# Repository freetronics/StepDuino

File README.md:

Freetronics StepDuino
=====================
Copyright 2013 Freetronics Pty Ltd  
Freetronics site:  www.freetronics.com  
Freetronics email: info@freetronics.com  

The StepDuino is an Arduino-compatible board with two onboard stepper
motor drivers, a 20x4 LCD, servo outputs, and an SD card slot. This
makes it ideal for mechatronics projects such as small robots or 2D
plotters.

It uses the same ATmega328P MCU as the Arduino Uno reference design,
and includes an ATmega16u2 USB-to-serial converter just like the Uno.
You can therefore program it the same way as you would an Uno, but
with the benefit of all the extra features built in to the StepDuino.

Features:

 * 2 x 4-wire stepper motor drivers
 * 20x4 LCD
 * Micro SD card slot
 * Analog inputs for use with Nintendo DS touch screen or other sensors

You can view more online at:

  http://www.freetronics.com/stepduino

INSTALLATION
------------
The design is saved as an EAGLE project. EAGLE PCB design software is
available from www.cadsoftusa.com free for non-commercial use. To use
this project download it and place the directory containing these files
into the "eagle" directory on your computer. Then open EAGLE and
navigate to Projects -> eagle -> StepDuino.

DISTRIBUTION
------------
The specific terms of distribution of this project are governed by the
license referenced below.

LICENSE
-------
Licensed under the TAPR Open Hardware License (www.tapr.org/OHL).
The "license" folder within this repository also contains a copy of
this license in plain text format.

CREDITS
-------
Designed by Luke Weston (reindeerflotilla@gmail.com) and Jonathan Oxer
(jon@freetronics.com)

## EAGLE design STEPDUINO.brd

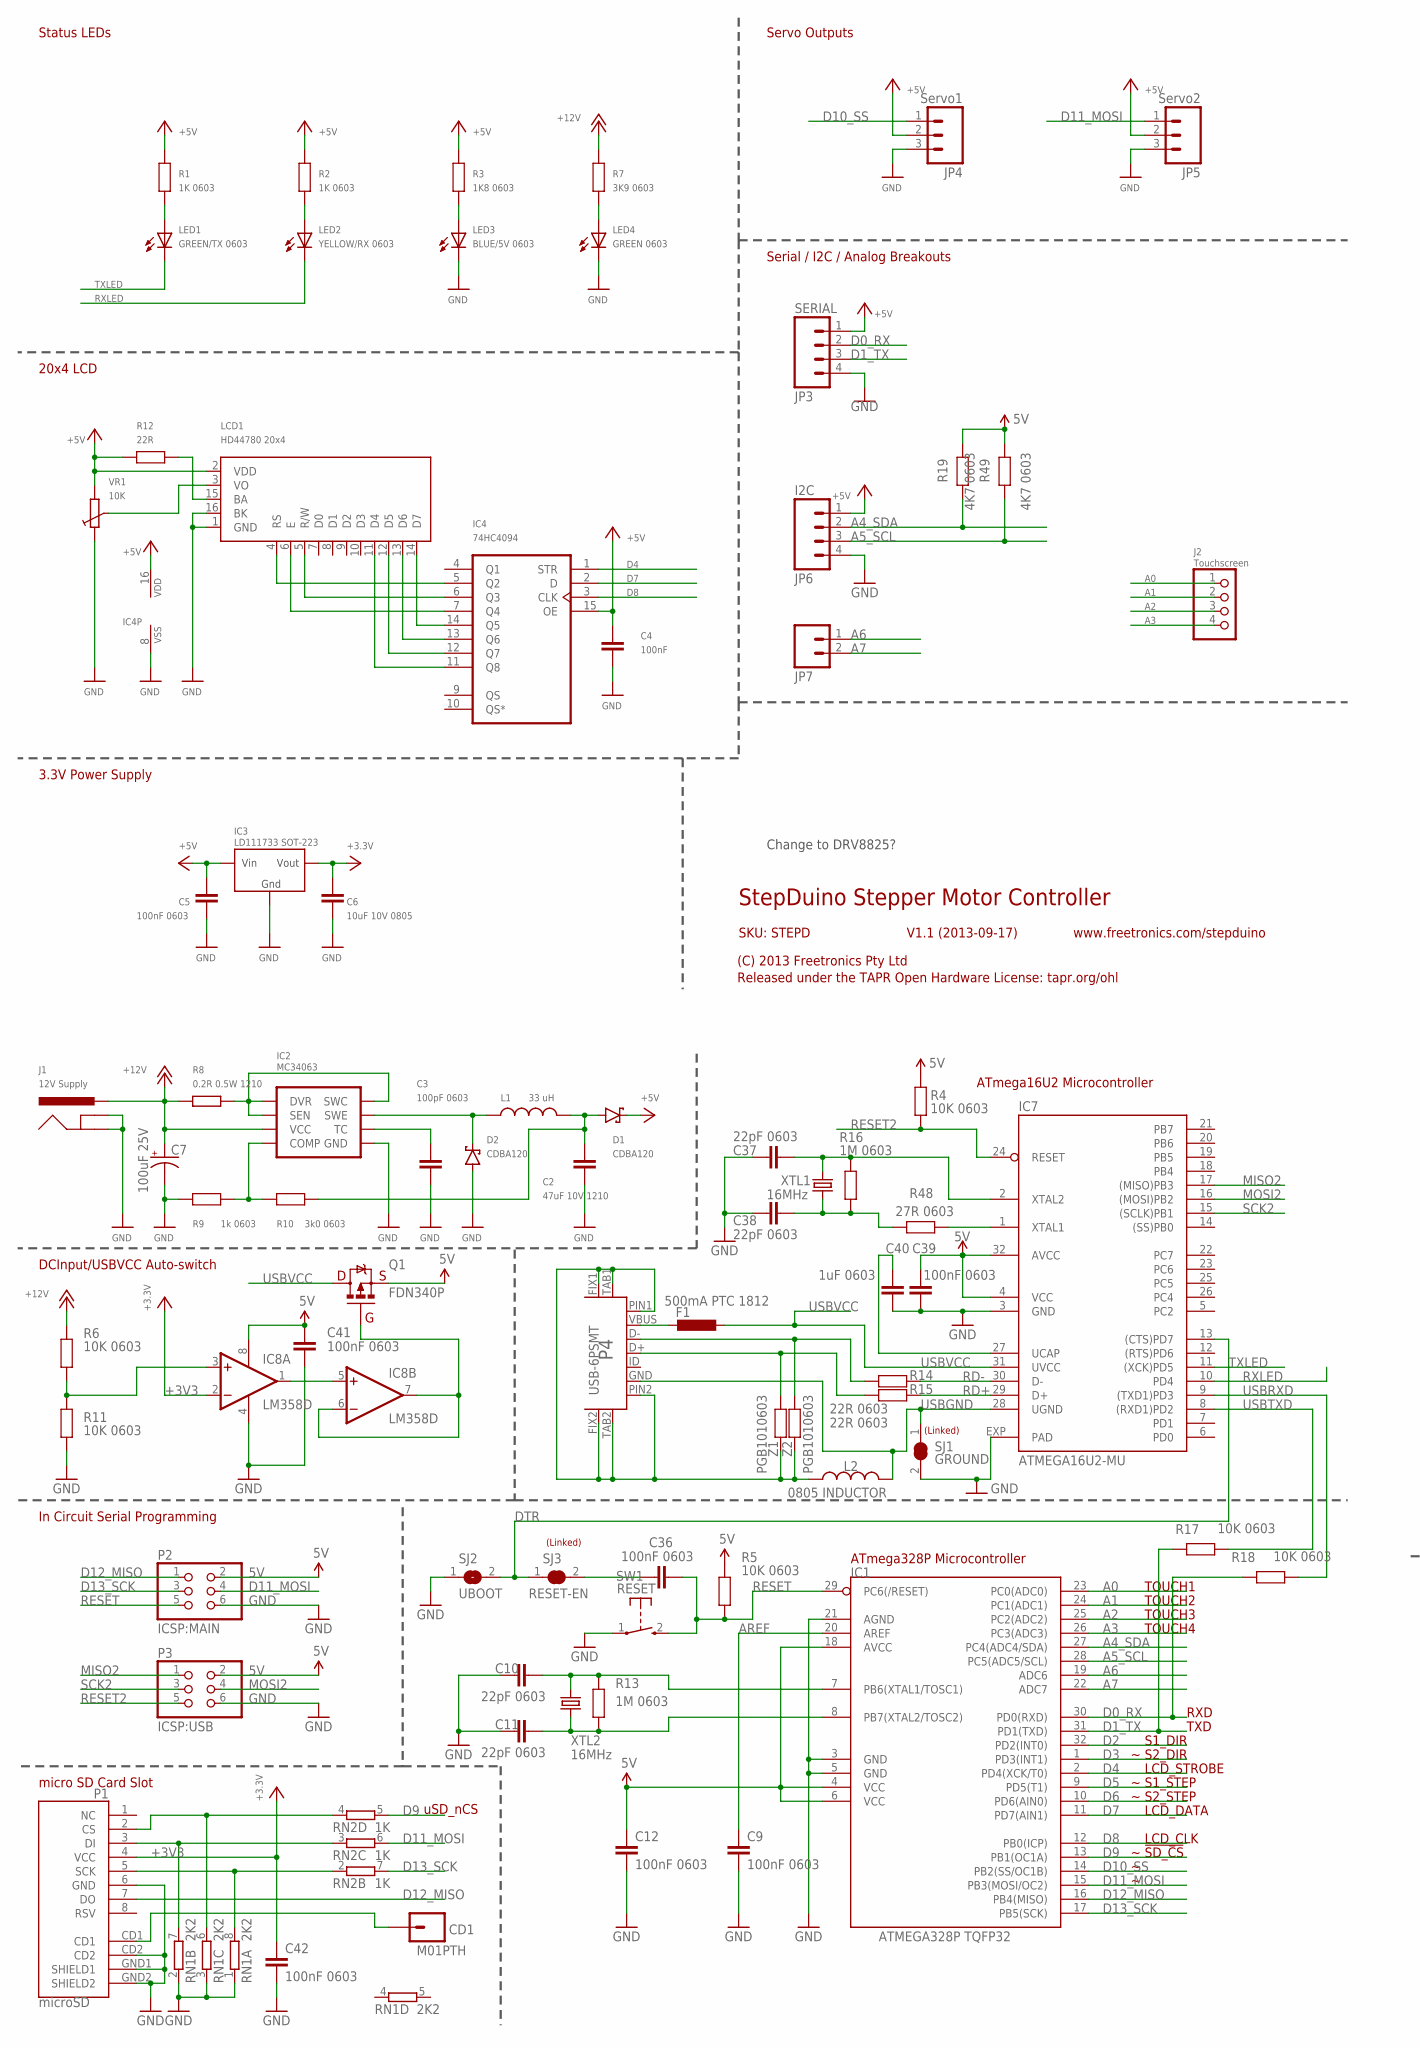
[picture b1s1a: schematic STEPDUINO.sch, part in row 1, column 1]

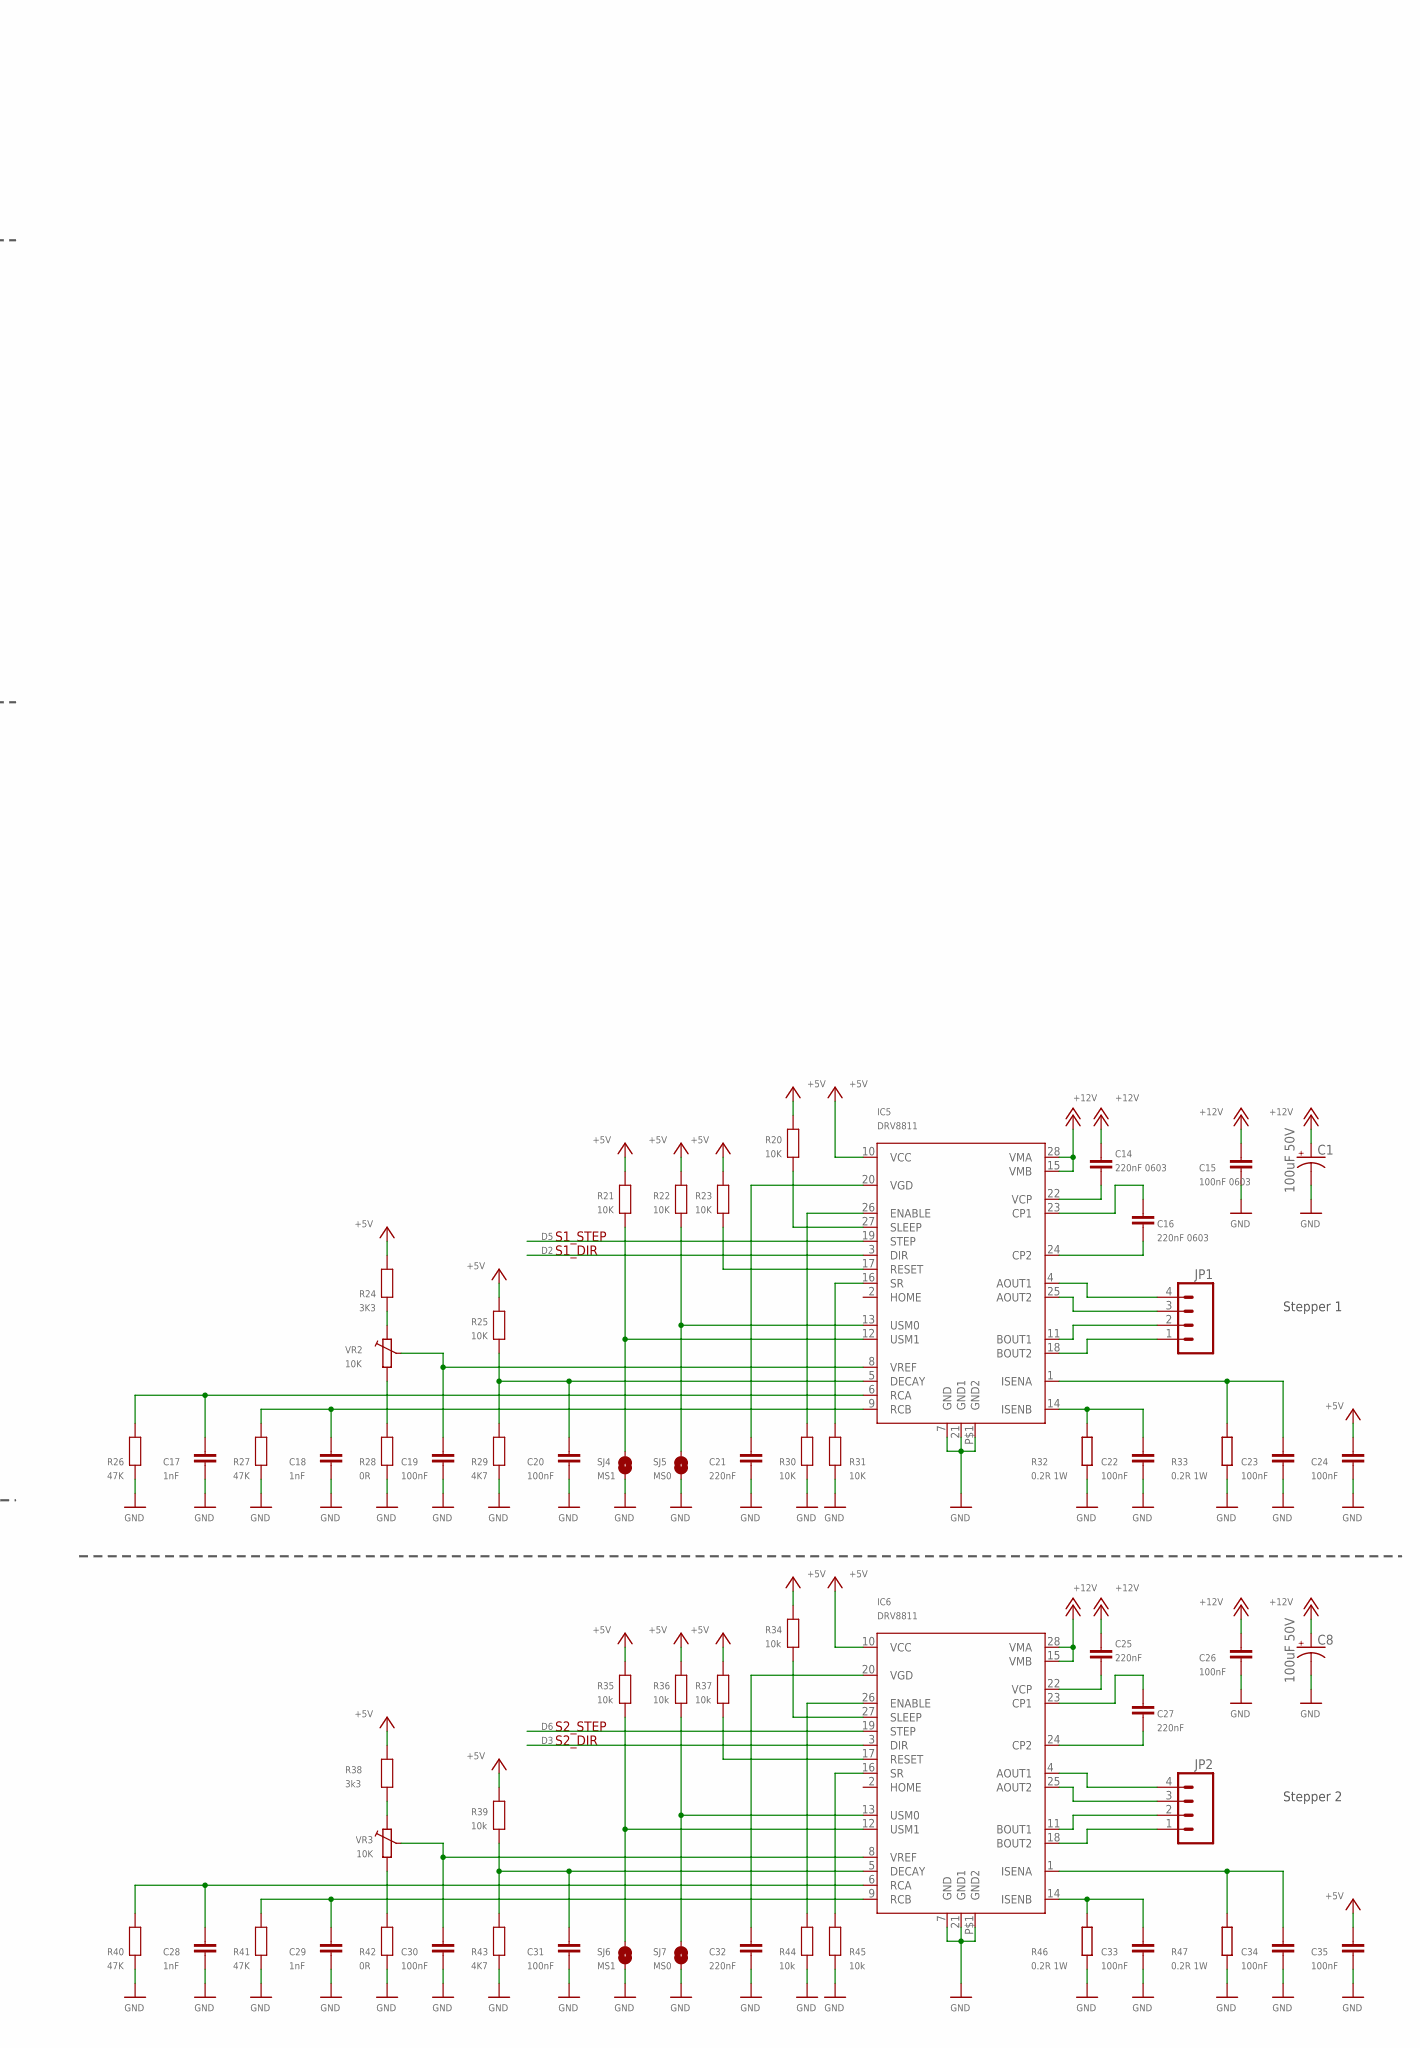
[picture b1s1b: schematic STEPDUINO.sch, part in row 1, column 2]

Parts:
C1, C8: 100uF 50V; PANASONIC_E
C2: 47uF 10V 1210; C1210
C3: 100pF 0603; 0603
C4, C19, C20, C22, C23, C24, C26, C30, C31, C33, C34, C35: 100nF; 0603
C5, C9, C12, C15, C36, C39, C41, C42: 100nF 0603; 0603
C6: 10uF 10V 0805; 0805
C7: 100uF 25V; PANASONIC_E
C10, C11, C37, C38: 22pF 0603; 0603
C14, C16: 220nF 0603; 0603
C17, C18, C28, C29: 1nF; 0603
C21, C25, C27, C32: 220nF; 0603
C40: 1uF 0603; 0603
CD1: M01PTH; 1X01
D1, D2: CDBA120; SMA
F1: 500mA PTC 1812; L1812
IC1: ATMEGA328P TQFP32; TQFP32-08
IC2: MC34063; SO08
IC3: LD111733 SOT-223; SOT223
IC4: 74HC4094; SO16@1
IC5, IC6: DRV8811; HTSSOP28
IC7: ATMEGA16U2-MU; ATMEL_QFN32
IC8: LM358D; SO08
J1: 12V Supply; POWER_JACK_PTH
J2: Touchscreen; 1X04
JP1, JP2: M04SCREW; SCREWTERMINAL-3.5MM-4
JP3: SERIAL; 1X04
JP4: Servo1; 1X03
JP5: Servo2; 1X03
JP6: I2C; 1X04
JP7: M02PTH; 1X02
L1: 33 uH; CR75
L2: 0805 INDUCTOR; 0805-LARGE
LCD1: HD44780 20x4; HDM20416L
LED1: GREEN/TX 0603; LED-0603
LED2: YELLOW/RX 0603; LED-0603
LED3: BLUE/5V 0603; LED-0603
LED4: GREEN 0603; LED-0603
P1: microSD; MICRO-SD-SOCKET-PP
P2: ICSP:MAIN; 2X03
P3: ICSP:USB; 2X03
P4: USB-6PSMT; USB-MICROB-MB05PMXX
Q1: FDN340P; SOT23
R1, R2: 1K 0603; 0603
R3: 1K8 0603; 0603
R4, R5, R6, R11: 10K 0603; 0603
R7: 3K9 0603; 0603
R8: 0.2R 0.5W 1210; R1210
R9: 1k 0603; 0603
R10: 3k0 0603; 0603
R12: 22R; 0603
R13, R16: 1M 0603; 0603
R14, R15: 22R 0603; 0603
R17, R18: 10K 0603; 0603@1
R19, R49: 4K7 0603; 0603
R20, R21, R22, R23, R25, R30, R31: 10K; 0603
R24: 3K3; 0603
R26, R27, R40, R41: 47K; 0603
R28, R42: 0R; 0603
R29, R43: 4K7; 0603
R32, R33, R46, R47: 0.2R 1W; R2010
R34, R35, R36, R37, R39, R44, R45: 10k; 0603
R38: 3k3; 0603
R48: 27R 0603; 0603
RN1: 2K2; CAY16
RN2: 1K; CAY16
SJ1: GROUND; SJC
SJ2: UBOOT; SJ
SJ3: RESET-EN; SJC
SJ4, SJ6: MS1; SJ
SJ5, SJ7: MS0; SJ
SW1: RESET; TACTILE_SWITCH_SMD_2PIN_TINY
VR1, VR2, VR3: 10K; CT6
XTL1, XTL2: 16MHz; HC49U-V
Z1, Z2: PGB1010603; 0603

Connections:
5V: C4.1, C5.1, C12.1, C24.1, C35.1, C39.1, C41.1, D1.K, IC1.4 (VCC), IC1.6 (VCC), IC1.18 (AVCC), IC3.3 (VIN), IC4.15 (OE), IC4.16 (VDD), IC5.10 (VCC), IC6.10 (VCC), IC7.4 (VCC), IC7.32 (AVCC), IC8.8 (V+), JP3.1, JP4.2, JP5.2, JP6.1, LCD1.2 (VDD), P2.2, P3.2, Q1.2 (S), R1.2, R2.2, R3.2, R4.2, R5.2, R12.2, R19.2, R20.2, R21.2, R22.2, R23.2, R24.2, R25.2, R34.2, R35.2, R36.2, R37.2, R38.2, R39.2, R49.2, VR1.A
+3V3: C6.1, C42.1, IC3.2 (VOUT), IC8.2 (-IN), P1.4 (VCC)
+12V: C1.+, C7.+, C8.+, C14.1, C15.1, C25.1, C26.1, IC2.6 (VCC), IC5.15 (VMB), IC5.28 (VMA), IC6.15 (VMB), IC6.28 (VMA), J1.PWR, R6.2, R7.2, R8.1
A0: IC1.23 (PC0(ADC0)), J2.1
A1: IC1.24 (PC1(ADC1)), J2.2
A2: IC1.25 (PC2(ADC2)), J2.3
A3: IC1.26 (PC3(ADC3)), J2.4
A4_SDA: IC1.27 (PC4(ADC4/SDA)), JP6.2, R19.1
A5_SCL: IC1.28 (PC5(ADC5/SCL)), JP6.3, R49.1
A6: IC1.19 (ADC6), JP7.1
A7: IC1.22 (ADC7), JP7.2
AREF: C9.1, IC1.20 (AREF)
D0_RX: IC1.30 (PD0(RXD)), JP3.2, R18.1
D1_TX: IC1.31 (PD1(TXD)), JP3.3, R17.1
D2: IC1.32 (PD2(INT0)), IC5.3 (DIR)
D3: IC1.1 (PD3(INT1)), IC6.3 (DIR)
D4: IC1.2 (PD4(XCK/T0)), IC4.1 (STR)
D5: IC1.9 (PD5(T1)), IC5.19 (STEP)
D6: IC1.10 (PD6(AIN0)), IC6.19 (STEP)
D7: IC1.11 (PD7(AIN1)), IC4.2 (D)
D8: IC1.12 (PB0(ICP)), IC4.3 (CLK)
D9: IC1.13 (PB1(OC1A)), RN2.5 (2)
D10_SS: IC1.14 (PB2(SS/OC1B)), JP4.1
D11_MOSI: IC1.15 (PB3(MOSI/OC2)), JP5.1, P2.4, RN2.6 (2)
D12_MISO: IC1.16 (PB4(MISO)), P1.7 (DO), P2.1
D13_SCK: IC1.17 (PB5(SCK)), P2.3, RN2.7 (2)
DTR: IC7.13 ((CTS)PD7), SJ2.2, SJ3.1
GND: C1.-, C2.2, C3.2, C4.2, C5.2, C6.2, C7.-, C8.-, C9.2, C10.1, C11.1, C12.2, C15.2, C17.2, C18.2, C19.2, C20.2, C21.2, C22.2, C23.2, C24.2, C26.2, C28.2, C29.2, C30.2, C31.2, C32.2, C33.2, C34.2, C35.2, C37.1, C38.1, C39.2, C40.2, C41.2, C42.2, D2.A, IC1.3 (GND), IC1.5 (GND), IC1.21 (AGND), IC2.4 (GND), IC3.1 (GND), IC4.8 (VSS), IC5.7 (GND), IC5.21 (GND1), IC5.P$1 (GND2), IC6.7 (GND), IC6.21 (GND1), IC6.P$1 (GND2), IC7.3 (GND), IC7.EXP (PAD), IC8.4 (V-), J1.GND, J1.GNDBREAK, JP3.4, JP4.3, JP5.3, JP6.4, LCD1.1 (GND), LCD1.16 (BK), LED3.C, LED4.C, P1.6 (GND), P1.CD2, P1.GND1 (SHIELD1), P1.GND2 (SHIELD2), P2.6, P3.6, R9.2, R11.1, R26.1, R27.1, R28.1, R29.1, R30.1, R31.1, R32.1, R33.1, R40.1, R41.1, R42.1, R43.1, R44.1, R45.1, R46.1, R47.1, RN1.1, RN1.2 (1), RN1.3 (1), SJ1.2, SJ2.1, SJ4.1, SJ5.1, SJ6.1, SJ7.1, SW1.1, VR1.E
MISO2: IC7.17 ((MISO)PB3), P3.1
MOSI2: IC7.16 ((MOSI)PB2), P3.4
unnamed: IC6.11 (BOUT1), JP2.2
unnamed: IC5.4 (AOUT1), JP1.4
unnamed: IC6.18 (BOUT2), JP2.1
unnamed: IC6.25 (AOUT2), JP2.3
unnamed: C27.2, IC6.24 (CP2)
unnamed: C27.1, IC6.23 (CP1)
unnamed: C25.2, IC6.22 (VCP)
unnamed: C32.1, IC6.20 (VGD)
unnamed: C10.2, IC1.7 (PB6(XTAL1/TOSC1)), R13.2, XTL2.2
unnamed: C34.1, IC6.1 (ISENA), R47.2
unnamed: C33.1, IC6.14 (ISENB), R46.2
unnamed: C31.1, IC6.5 (DECAY), R39.1, R43.2
unnamed: C28.1, IC6.6 (RCA), R40.2
unnamed: C16.2, IC5.24 (CP2)
unnamed: C16.1, IC5.23 (CP1)
unnamed: IC5.16 (SR), R31.2
unnamed: C29.1, IC6.9 (RCB), R41.2
unnamed: IC5.18 (BOUT2), JP1.1
unnamed: IC5.11 (BOUT1), JP1.2
unnamed: IC5.25 (AOUT2), JP1.3
unnamed: C14.2, IC5.22 (VCP)
unnamed: C20.1, IC5.5 (DECAY), R25.1, R29.2
unnamed: C21.1, IC5.20 (VGD)
unnamed: C17.1, IC5.6 (RCA), R26.2
unnamed: C11.2, IC1.8 (PB7(XTAL2/TOSC2)), R13.1, XTL2.1
unnamed: LED3.A, R3.1
unnamed: LED2.A, R2.1
unnamed: LED1.A, R1.1
unnamed: IC2.1 (SWC), IC2.7 (SEN), IC2.8 (DVR), R8.2
unnamed: IC7.1 (XTAL1), R48.1
unnamed: L2.1, P4.FIX1, P4.FIX2, P4.PIN1, P4.PIN2, P4.TAB1, P4.TAB2, Z1.2, Z2.2
unnamed: P4.D+, R15.2, Z1.1
unnamed: P4.D-, R14.2, Z2.1
unnamed: LED4.A, R7.1
unnamed: C3.1, IC2.3 (TC)
unnamed: IC2.5 (COMP), R9.1, R10.2
unnamed: D2.K, IC2.2 (SWE), L1.P$1 (1)
unnamed: C23.1, IC5.1 (ISENA), R33.2
unnamed: C22.1, IC5.14 (ISENB), R32.2
unnamed: C18.1, IC5.9 (RCB), R27.2
unnamed: IC5.27 (SLEEP), R20.1
unnamed: IC4.5 (Q2), LCD1.4 (RS)
unnamed: IC4.6 (Q3), LCD1.5 (R/W)
unnamed: IC4.7 (Q4), LCD1.6 (E)
unnamed: IC4.11 (Q8), LCD1.11 (D4)
unnamed: IC4.12 (Q7), LCD1.12 (D5)
unnamed: IC4.13 (Q6), LCD1.13 (D6)
unnamed: IC4.14 (Q5), LCD1.14 (D7)
unnamed: IC5.17 (RESET), R23.1
unnamed: LCD1.3 (VO), VR1.S
unnamed: LCD1.15 (BA), R12.1
unnamed: R24.1, VR2.E
unnamed: R28.2, VR2.A
unnamed: IC8.3 (+IN), R6.1, R11.2
unnamed: IC8.6 (-IN), IC8.7 (OUT), Q1.1 (G)
unnamed: C19.1, IC5.8 (VREF), VR2.S
unnamed: IC5.26 (ENABLE), R30.2
unnamed: IC5.12 (USM1), R21.1, SJ4.2
unnamed: IC5.13 (USM0), R22.1, SJ5.2
unnamed: IC6.27 (SLEEP), R34.1
unnamed: IC6.17 (RESET), R37.1
unnamed: R38.1, VR3.E
unnamed: R42.2, VR3.A
unnamed: C30.1, IC6.8 (VREF), VR3.S
unnamed: IC6.26 (ENABLE), R44.2
unnamed: IC6.12 (USM1), R35.1, SJ6.2
unnamed: IC6.13 (USM0), R36.1, SJ7.2
unnamed: IC6.16 (SR), R45.2
unnamed: IC6.4 (AOUT1), JP2.4
unnamed: IC8.1 (OUT), IC8.5 (+IN)
unnamed: P1.2 (CS), RN1.6 (2), RN2.4 (1)
unnamed: P1.3 (DI), RN1.7 (2), RN2.3 (1)
unnamed: P1.5 (SCK), RN1.8 (2), RN2.2 (1)
unnamed: CD1.1, P1.CD1
unnamed: C36.1, SJ3.2
unnamed: C37.2, IC7.2 (XTAL2), R16.2, XTL1.2
unnamed: C38.2, R16.1, R48.2, XTL1.1
unnamed: F1.1, P4.VBUS
unnamed: C40.1, IC7.27 (UCAP)
RD+: IC7.29 (D+), R15.1
RD-: IC7.30 (D-), R14.1
REG_5V: C2.1, D1.A, L1.P$2 (2), R10.1
RESET: C36.2, IC1.29 (PC6(/RESET)), P2.5, R5.1, SW1.2 (S)
RESET2: IC7.24 (RESET), P3.5, R4.1
RXLED: IC7.10 (PD4), LED2.C
SCK2: IC7.15 ((SCLK)PB1), P3.3
TXLED: IC7.11 ((XCK)PD5), LED1.C
USBGND: IC7.28 (UGND), L2.2, P4.GND, SJ1.1
USBRXD: IC7.9 ((TXD1)PD3), R18.2
USBTXD: IC7.8 ((RXD1)PD2), R17.2
USBVCC: F1.2, IC7.31 (UVCC), Q1.3 (D)

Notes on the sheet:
StepDuino Stepper Motor Controller
V1.1 (2013-09-17)
(C) 2013 Freetronics Pty Ltd
Released under the TAPR Open Hardware License: tapr.org/ohl
www.freetronics.com/stepduino
Stepper 1
Stepper 2
ATmega328P Microcontroller
ATmega16U2 Microcontroller
DCInput/USBVCC Auto-switch
uSD_nCS
In Circuit Serial Programming
micro SD Card Slot
(Linked)
!SD_CS
TOUCH1
TOUCH2
TOUCH3
TOUCH4
TXD
RXD
S1_DIR
S2_DIR
S2_STEP
S1_STEP
LCD_CLK
LCD_DATA
LCD_STROBE
Change to DRV8825?
SKU: STEPD
Serial / I2C / Analog Breakouts
Servo Outputs
3.3V Power Supply
20x4 LCD
Status LEDs

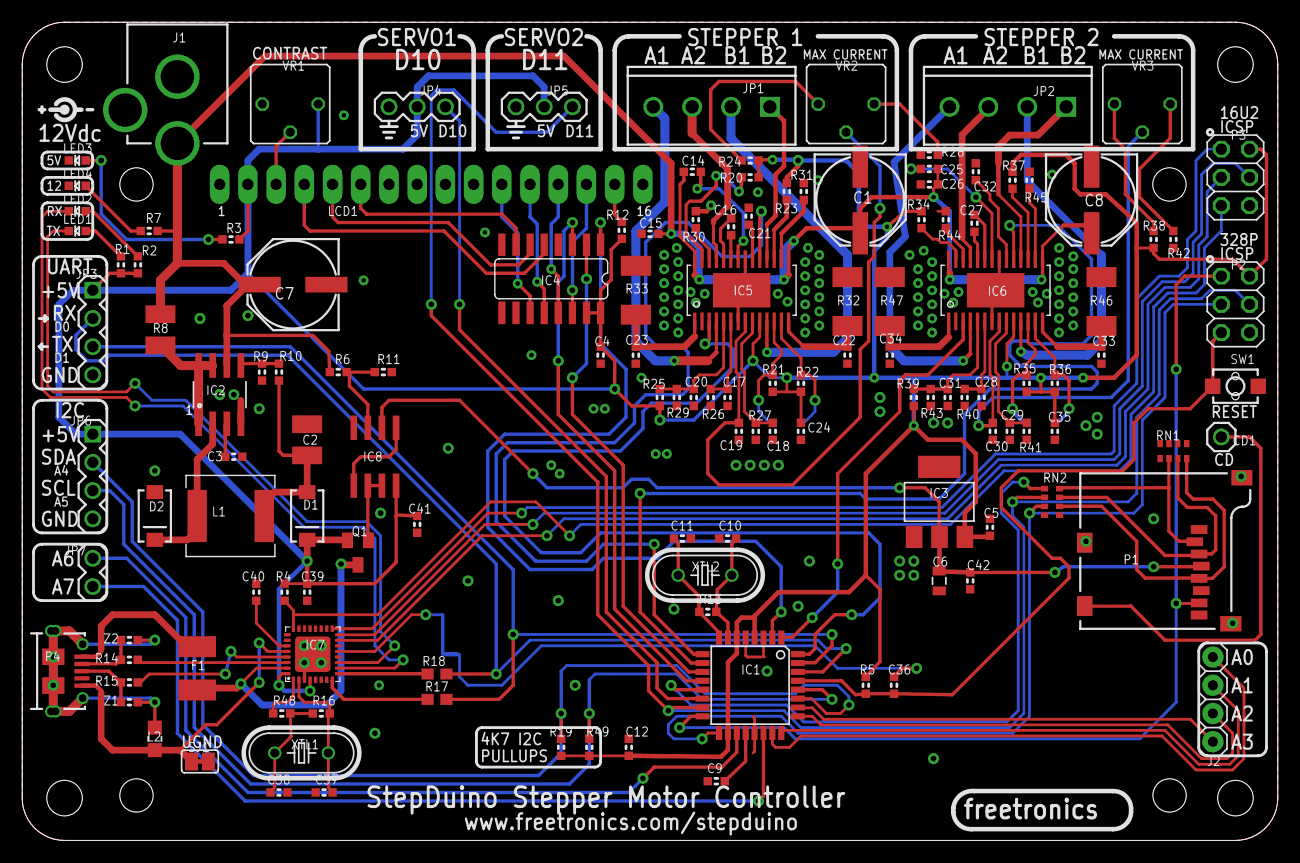
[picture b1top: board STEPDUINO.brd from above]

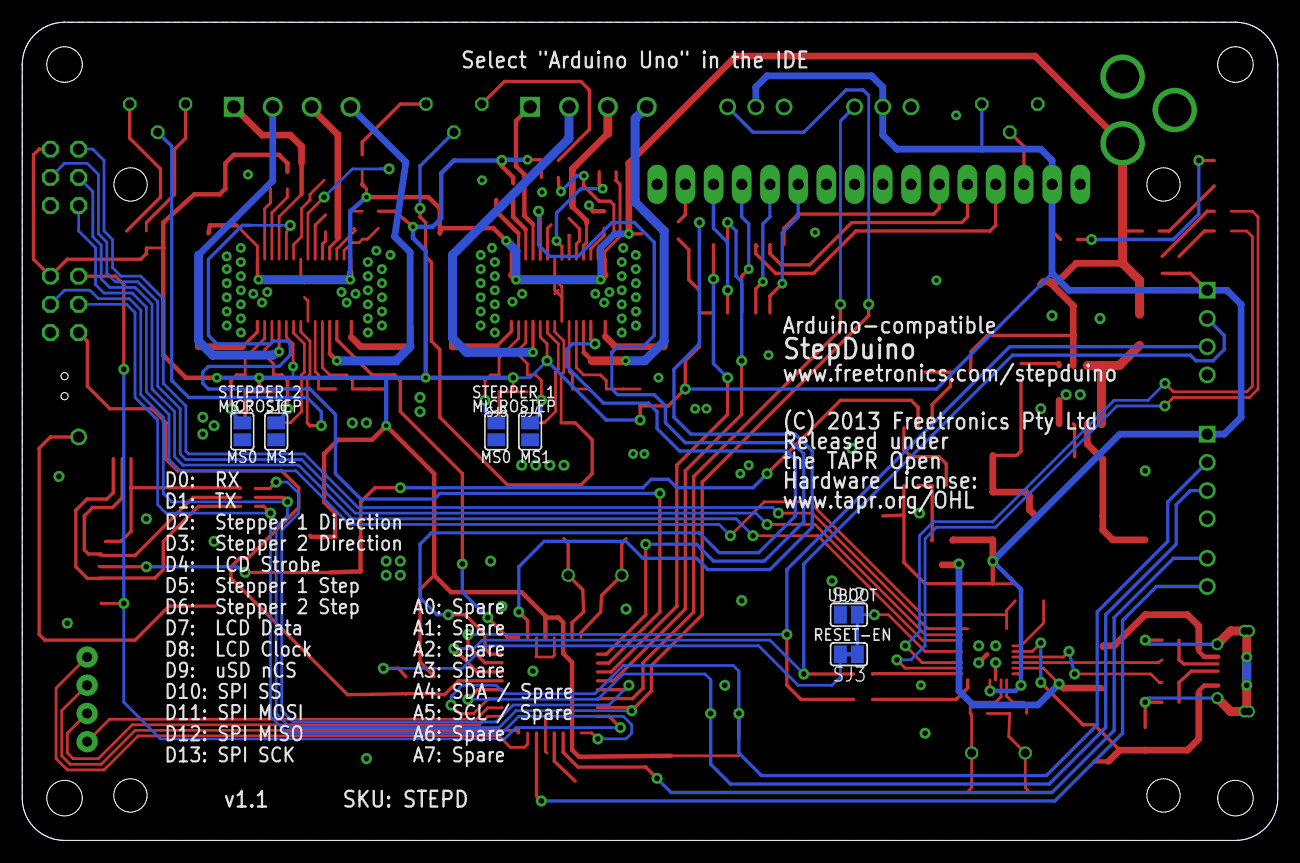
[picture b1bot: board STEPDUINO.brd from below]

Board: 2 copper layers, 113.0 x 73.7 mm, 140 parts (6 on the bottom side), 121 nets.

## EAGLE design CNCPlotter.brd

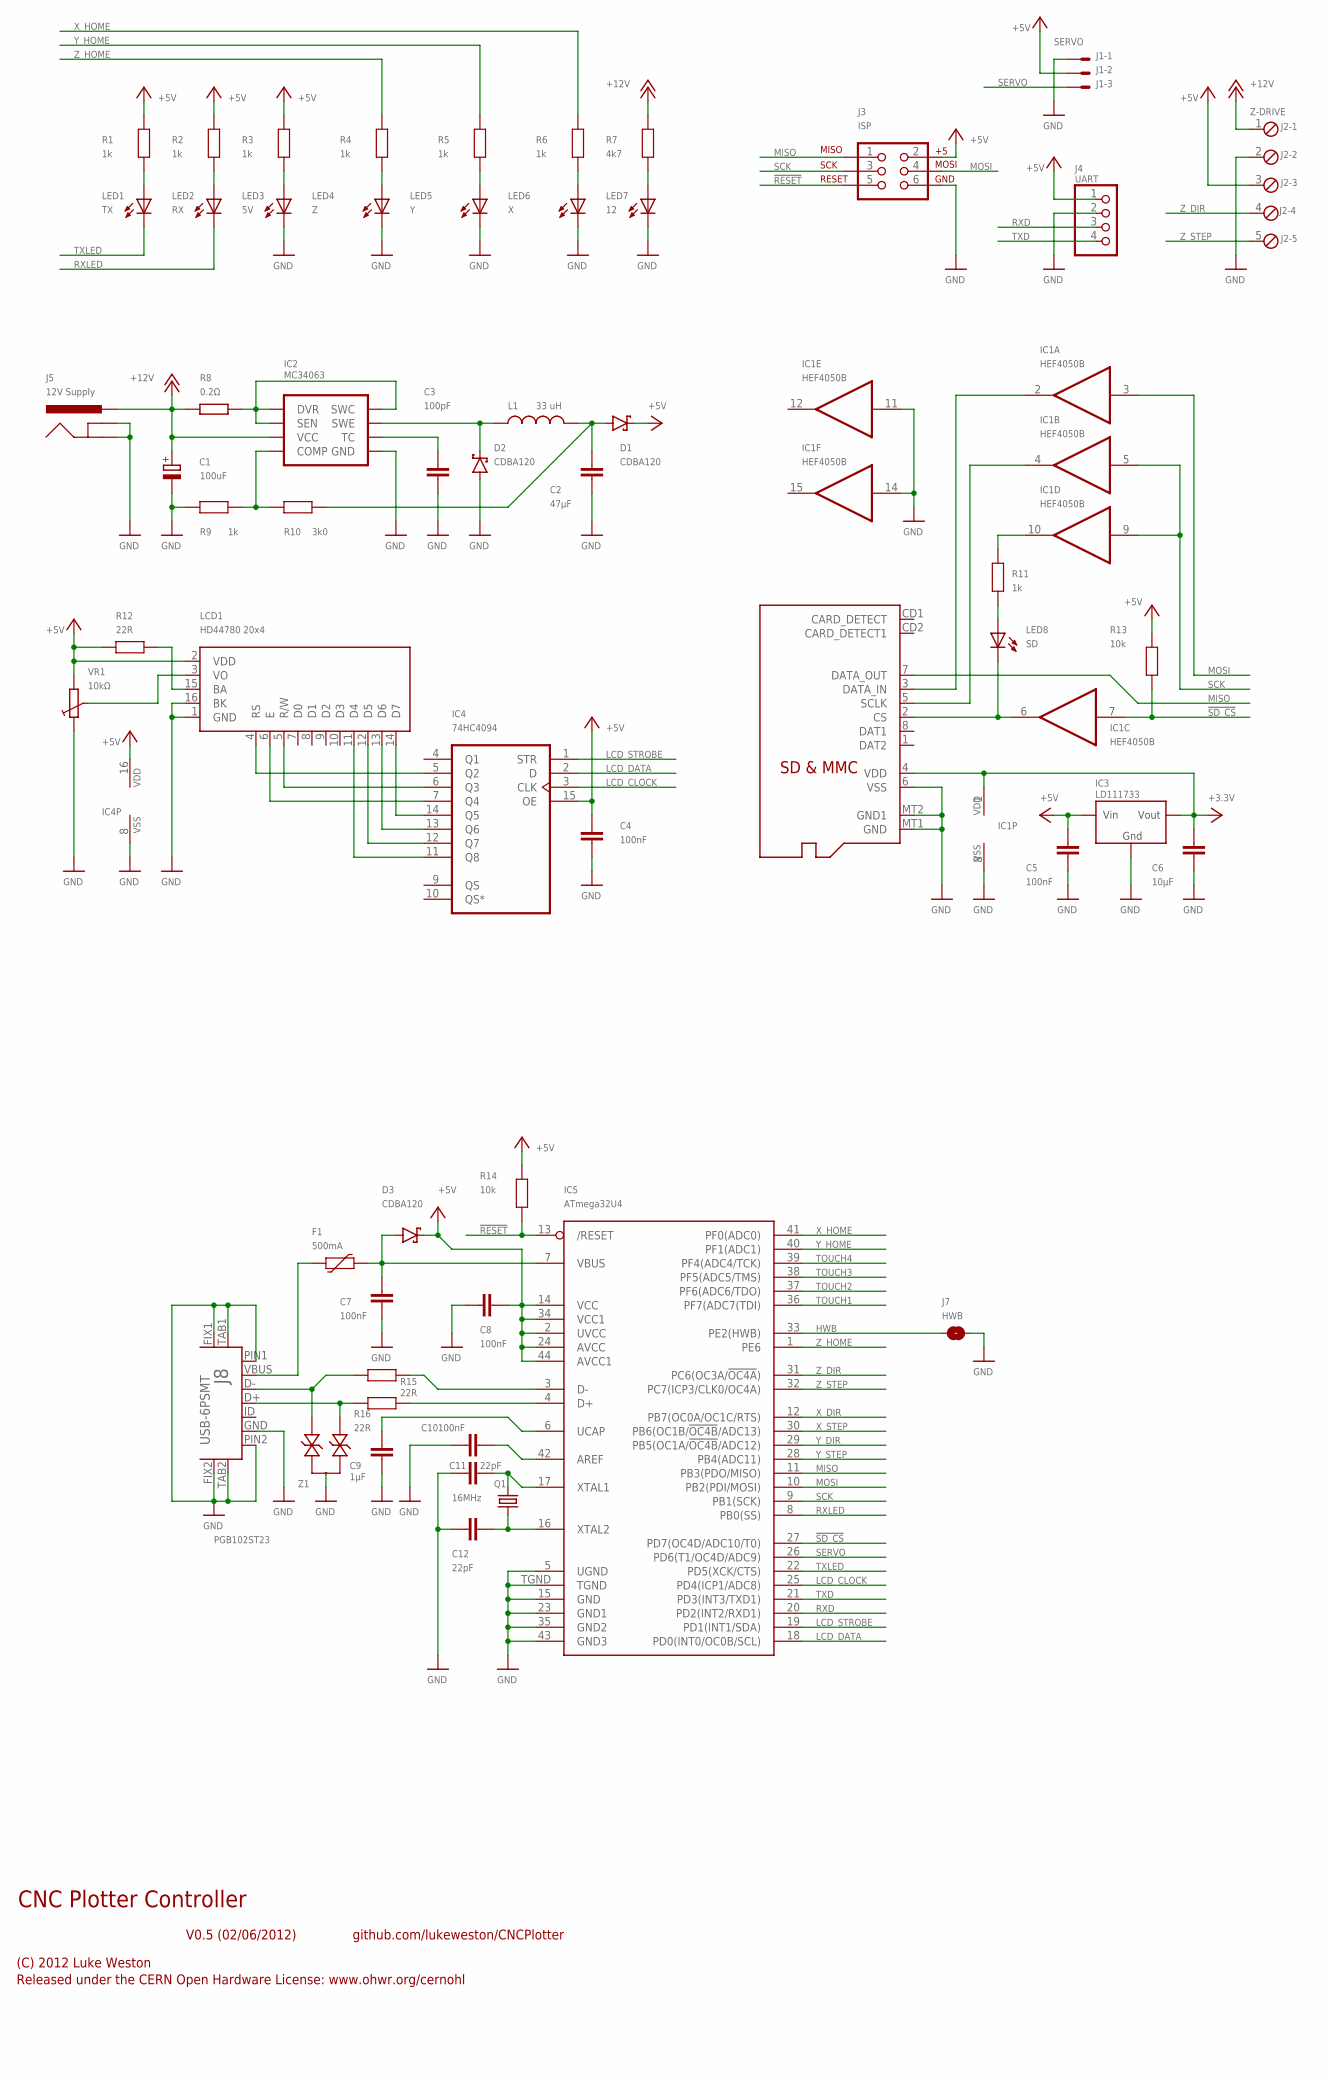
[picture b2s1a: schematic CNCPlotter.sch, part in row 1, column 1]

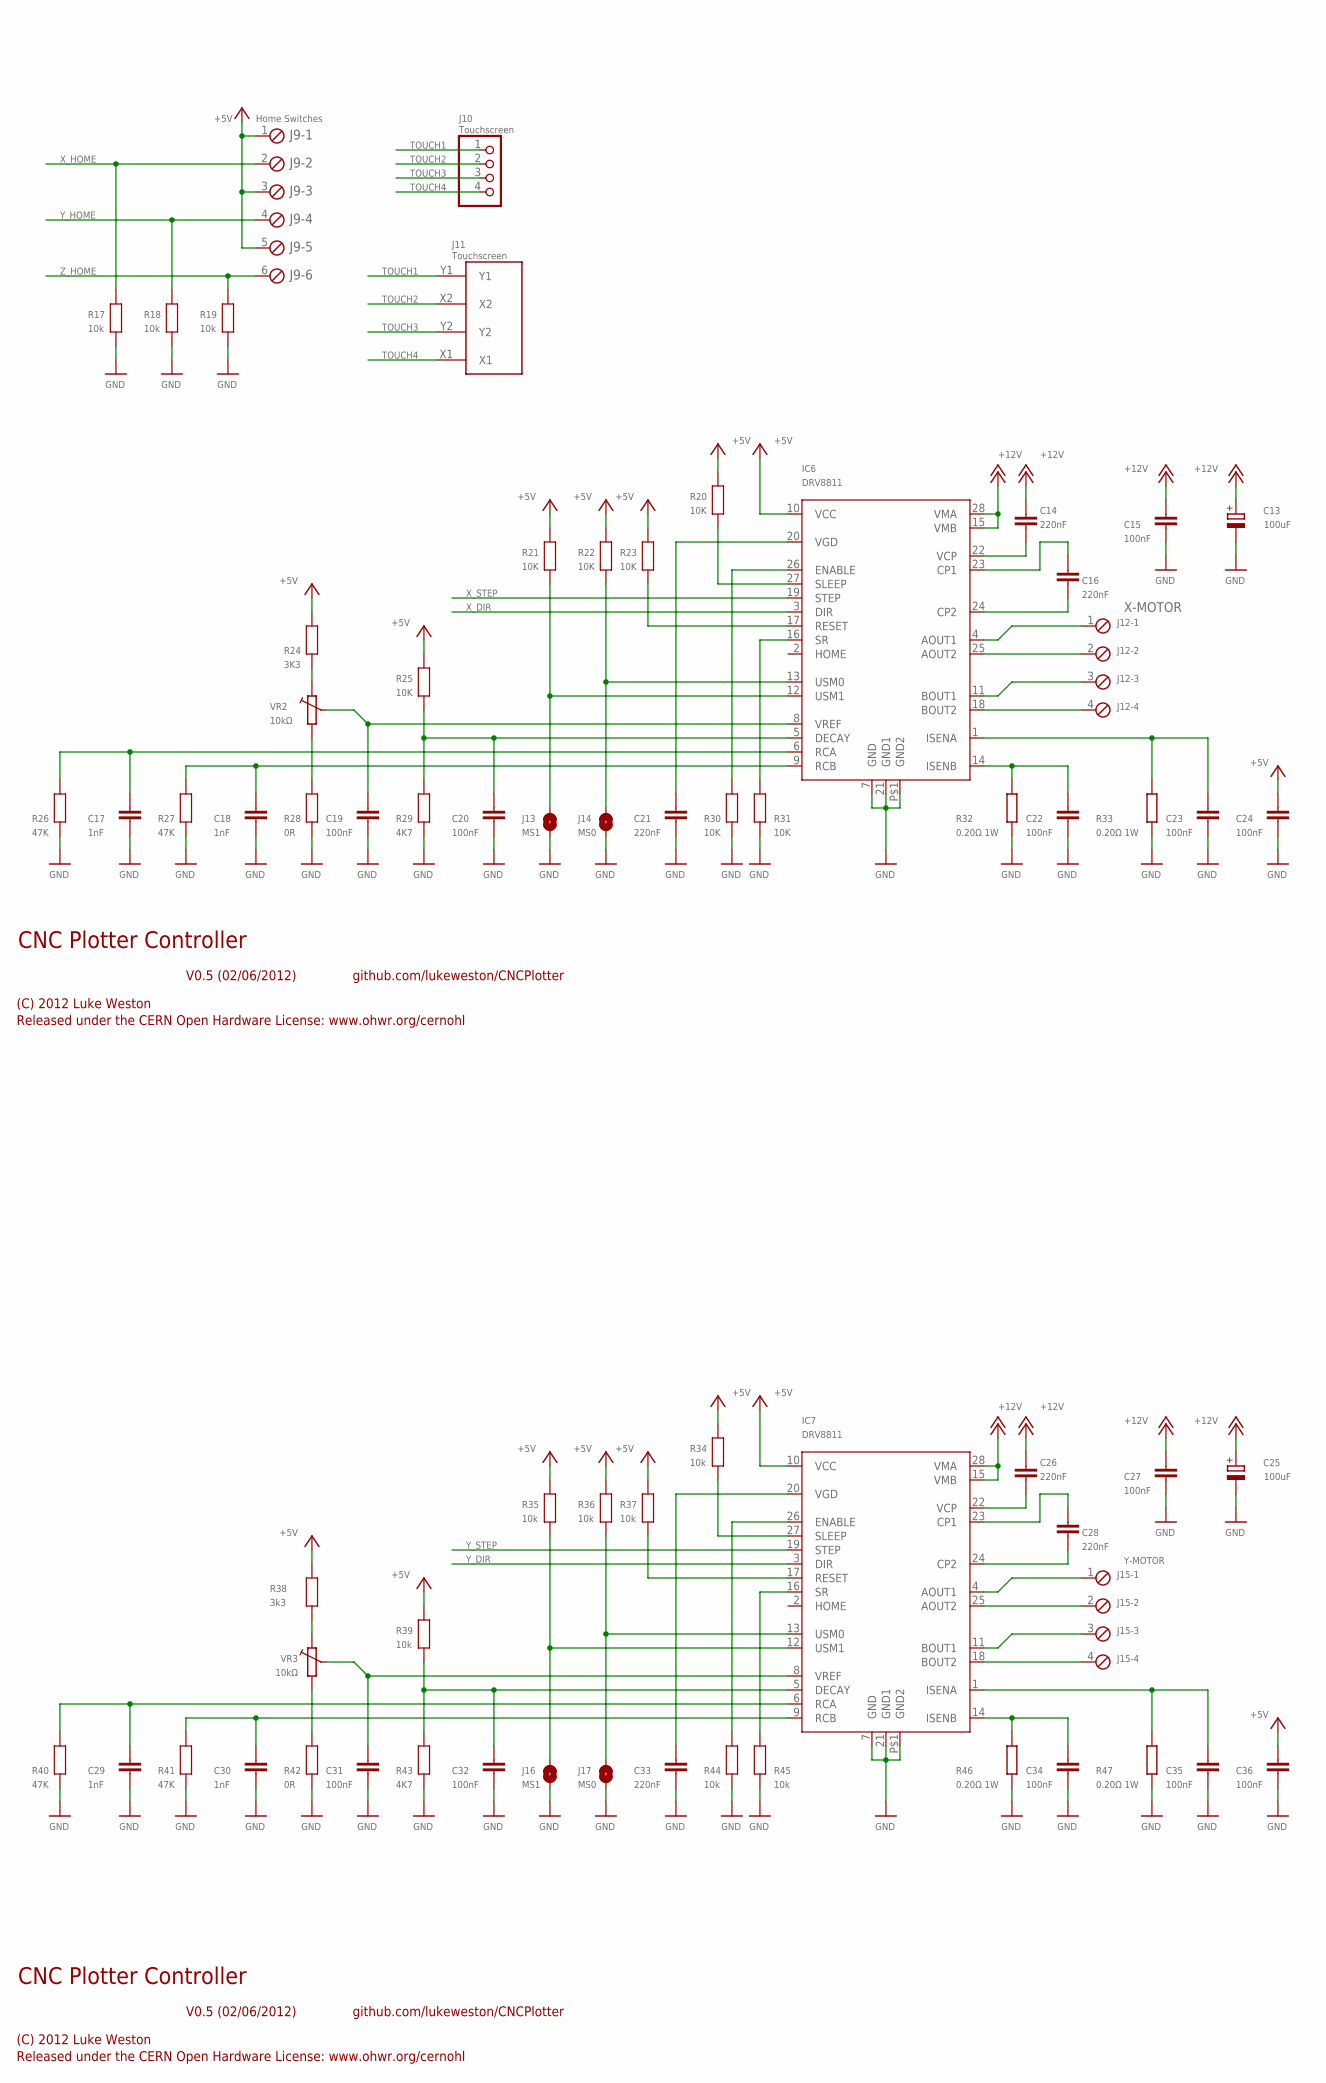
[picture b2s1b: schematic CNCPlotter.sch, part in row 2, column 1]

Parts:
C1, C13, C25: 100uF; E2,5-6
C2: 47µF; C1210
C3: 100pF; 0603
C4, C5, C7, C8, C10, C15, C19, C20, C22, C23, C24, C27, C31, C32, C34, C35, C36: 100nF; 0603
C6: 10µF; 0805
C9: 1µF; 0603
C11, C12: 22pF; 0603
C14, C16, C21, C26, C28, C33: 220nF; 0603
C17, C18, C29, C30: 1nF; 0603
D1, D2, D3: CDBA120; SMA
F1: 500mA; 1812
IC1: HEF4050B; SO16
IC2: MC34063; SO08
IC3: LD111733; SOT223
IC4: 74HC4094; SO16@1
IC5: ATmega32U4; QFN-44N
IC6, IC7: DRV8811; HTSSOP28
J1: SERVO; 22-23-2031
J2: Z-DRIVE; 5POL254
J3: ISP; 2X3-NS
J4: UART; 1X04
J5: 12V Supply; POWER_JACK_PTH
J6: MicroSD Card; ADAFRUIT_MICROSD
J7: HWB; SJ
J8: USB-6PSMT; USB-MICROB-MB05PMXX
J9: Home Switches; 6POL254
J10: Touchscreen; 1X04
J11: Touchscreen; DS_TOUCH_CONNECTOR
J12: X-MOTOR; 4POL254
J13, J16: MS1; SJ
J14, J17: MS0; SJ
J15: Y-MOTOR; 4POL254
L1: 33 uH; CR75
LCD1: HD44780 20x4; HDM20416L
LED1: TX; LED-0603
LED2: RX; LED-0603
LED3: 5V; LED-0603
LED4: Z; LED-0603
LED5: Y; LED-0603
LED6: X; LED-0603
LED7: 12; LED-0603
LED8: SD; LED-0603
Q1: 16MHz; HC49US
R1, R2, R3, R4, R5, R6, R9, R11: 1k; 0603
R7: 4k7; 0603
R8: 0.2Ω; R1210
R10: 3k0; 0603
R12, R15, R16: 22R; 0603
R13, R14, R17, R18, R19, R34, R35, R36, R37, R39, R44, R45: 10k; 0603
R20, R21, R22, R23, R25, R30, R31: 10K; 0603
R24: 3K3; 0603
R26, R27, R40, R41: 47K; 0603
R28, R42: 0R; 0603
R29, R43: 4K7; 0603
R32, R33, R46, R47: 0.20Ω 1W; R2010
R38: 3k3; 0603
VR1, VR2, VR3: 10kΩ; CT6
Z1: PGB102ST23; SOT23-3

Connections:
!RESET: IC5.13 (/RESET), J3.5, R14.1
!SD_CS: IC1.7 (I), IC5.27 (PD7(OC4D/ADC10/T0)), R13.1
+5V: C4.1, C5.1, C8.2, C24.1, C36.1, D1.K, D3.K, IC3.3 (VIN), IC4.15 (OE), IC4.16 (VDD), IC5.2 (UVCC), IC5.14 (VCC), IC5.24 (AVCC), IC5.34 (VCC1), IC5.44 (AVCC1), IC6.10 (VCC), IC7.10 (VCC), J1.2, J2.3, J3.2, J4.1, J9.1, J9.3, J9.5, LCD1.2 (VDD), R1.2, R2.2, R3.2, R12.2, R13.2, R14.2, R20.2, R21.2, R22.2, R23.2, R24.2, R25.2, R34.2, R35.2, R36.2, R37.2, R38.2, R39.2, VR1.A
+12V: C1.+, C13.+, C14.1, C15.1, C25.+, C26.1, C27.1, IC2.6 (VCC), IC6.15 (VMB), IC6.28 (VMA), IC7.15 (VMB), IC7.28 (VMA), J2.1, J5.PWR, R7.2, R8.1
FOO: IC1.6 (O), J6.2 (CS), LED8.C
GND: C1.-, C2.2, C3.2, C4.2, C5.2, C6.2, C7.2, C8.1, C9.1, C10.1, C11.1, C12.1, C13.-, C15.2, C17.2, C18.2, C19.2, C20.2, C21.2, C22.2, C23.2, C24.2, C25.-, C27.2, C29.2, C30.2, C31.2, C32.2, C33.2, C34.2, C35.2, C36.2, D2.A, IC1.8 (VSS), IC1.11 (I), IC1.14 (I), IC2.4 (GND), IC3.1 (GND), IC4.8 (VSS), IC5.5 (UGND), IC5.15 (GND), IC5.23 (GND1), IC5.35 (GND2), IC5.43 (GND3), IC5.TGND, IC6.7 (GND), IC6.21 (GND1), IC6.P$1 (GND2), IC7.7 (GND), IC7.21 (GND1), IC7.P$1 (GND2), J1.1, J2.2, J3.6, J4.2, J5.GND, J5.GNDBREAK, J6.6 (VSS), J6.MT1 (GND), J6.MT2 (GND1), J7.1, J8.FIX1, J8.FIX2, J8.GND, J8.PIN1, J8.PIN2, J8.TAB1, J8.TAB2, J13.1, J14.1, J16.1, J17.1, LCD1.1 (GND), LCD1.16 (BK), LED3.C, LED4.C, LED5.C, LED6.C, LED7.C, R9.2, R17.2, R18.2, R19.2, R26.1, R27.1, R28.1, R29.1, R30.1, R31.1, R32.1, R33.1, R40.1, R41.1, R42.1, R43.1, R44.1, R45.1, R46.1, R47.1, VR1.E, Z1.3
HWB: IC5.33 (PE2(HWB)), J7.2
LCD_CLOCK: IC4.3 (CLK), IC5.25 (PD4(ICP1/ADC8))
LCD_DATA: IC4.2 (D), IC5.18 (PD0(INT0/OC0B/SCL))
LCD_STROBE: IC4.1 (STR), IC5.19 (PD1(INT1/SDA))
MISO: IC5.11 (PB3(PDO/MISO)), J3.1, J6.7 (DATA_OUT)
MOSI: IC1.3 (I), IC5.10 (PB2(PDI/MOSI)), J3.4
MOSI_3.3V: IC1.2 (O), J6.3 (DATA_IN)
unnamed: IC7.4 (AOUT1), J15.1
unnamed: F1.1, J8.VBUS
unnamed: IC6.4 (AOUT1), J12.1
unnamed: IC7.18 (BOUT2), J15.4
unnamed: IC7.11 (BOUT1), J15.3
unnamed: IC7.25 (AOUT2), J15.2
unnamed: C28.2, IC7.24 (CP2)
unnamed: C28.1, IC7.23 (CP1)
unnamed: C26.2, IC7.22 (VCP)
unnamed: C33.1, IC7.20 (VGD)
unnamed: C10.2, IC5.42 (AREF)
unnamed: LED4.A, R4.1
unnamed: C35.1, IC7.1 (ISENA), R47.2
unnamed: C34.1, IC7.14 (ISENB), R46.2
unnamed: C32.1, IC7.5 (DECAY), R39.1, R43.2
unnamed: C29.1, IC7.6 (RCA), R40.2
unnamed: C16.2, IC6.24 (CP2)
unnamed: C16.1, IC6.23 (CP1)
unnamed: IC6.16 (SR), R31.2
unnamed: C30.1, IC7.9 (RCB), R41.2
unnamed: IC6.18 (BOUT2), J12.4
unnamed: IC6.11 (BOUT1), J12.3
unnamed: IC6.25 (AOUT2), J12.2
unnamed: C14.2, IC6.22 (VCP)
unnamed: C20.1, IC6.5 (DECAY), R25.1, R29.2
unnamed: C21.1, IC6.20 (VGD)
unnamed: C17.1, IC6.6 (RCA), R26.2
unnamed: C9.2, IC5.6 (UCAP)
unnamed: LED3.A, R3.1
unnamed: LED2.A, R2.1
unnamed: LED1.A, R1.1
unnamed: IC2.1 (SWC), IC2.7 (SEN), IC2.8 (DVR), R8.2
unnamed: J8.D+, R16.2, Z1.1
unnamed: J8.D-, R15.2, Z1.2
unnamed: C11.2, IC5.17 (XTAL1), Q1.2
unnamed: C12.2, IC5.16 (XTAL2), Q1.1
unnamed: IC5.4 (D+), R16.1
unnamed: IC5.3 (D-), R15.1
unnamed: LED5.A, R5.1
unnamed: C7.1, D3.A, F1.2, IC5.7 (VBUS)
unnamed: LED6.A, R6.1
unnamed: LED7.A, R7.1
unnamed: C3.1, IC2.3 (TC)
unnamed: IC2.5 (COMP), R9.1, R10.2
unnamed: D2.K, IC2.2 (SWE), L1.P$1 (1)
unnamed: C23.1, IC6.1 (ISENA), R33.2
unnamed: C22.1, IC6.14 (ISENB), R32.2
unnamed: C18.1, IC6.9 (RCB), R27.2
unnamed: IC6.27 (SLEEP), R20.1
unnamed: IC4.5 (Q2), LCD1.4 (RS)
unnamed: IC4.6 (Q3), LCD1.5 (R/W)
unnamed: IC4.7 (Q4), LCD1.6 (E)
unnamed: IC4.11 (Q8), LCD1.11 (D4)
unnamed: IC4.12 (Q7), LCD1.12 (D5)
unnamed: IC4.13 (Q6), LCD1.13 (D6)
unnamed: IC4.14 (Q5), LCD1.14 (D7)
unnamed: IC6.17 (RESET), R23.1
unnamed: LCD1.3 (VO), VR1.S
unnamed: LCD1.15 (BA), R12.1
unnamed: R24.1, VR2.E
unnamed: R28.2, VR2.A
unnamed: LED8.A, R11.1
unnamed: IC1.10 (O), R11.2
unnamed: C19.1, IC6.8 (VREF), VR2.S
unnamed: IC6.26 (ENABLE), R30.2
unnamed: IC6.12 (USM1), J13.2, R21.1
unnamed: IC6.13 (USM0), J14.2, R22.1
unnamed: IC7.27 (SLEEP), R34.1
unnamed: IC7.17 (RESET), R37.1
unnamed: R38.1, VR3.E
unnamed: R42.2, VR3.A
unnamed: C31.1, IC7.8 (VREF), VR3.S
unnamed: IC7.26 (ENABLE), R44.2
unnamed: IC7.12 (USM1), J16.2, R35.1
unnamed: IC7.13 (USM0), J17.2, R36.1
unnamed: IC7.16 (SR), R45.2
REG_5V: C2.1, D1.A, L1.P$2 (2), R10.1
RXD: IC5.20 (PD2(INT2/RXD1)), J4.3
RXLED: IC5.8 (PB0(SS)), LED2.C
SCK: IC1.5 (I), IC1.9 (I), IC5.9 (PB1(SCK)), J3.3
SCK_3.3V: IC1.4 (O), J6.5 (SCLK)
SERVO: IC5.26 (PD6(T1/OC4D/ADC9)), J1.3
TOUCH1: IC5.36 (PF7(ADC7(TDI)), J10.1, J11.Y1
TOUCH2: IC5.37 (PF6(ADC6/TDO)), J10.2, J11.X2
TOUCH3: IC5.38 (PF5(ADC5/TMS)), J10.3, J11.Y2
TOUCH4: IC5.39 (PF4(ADC4/TCK)), J10.4, J11.X1
TXD: IC5.21 (PD3(INT3/TXD1)), J4.4
TXLED: IC5.22 (PD5(XCK/CTS)), LED1.C
VDD: C6.1, IC1.1 (VDD), IC3.2 (VOUT), J6.4 (VDD)
X_DIR: IC5.12 (PB7(OC0A/OC1C/RTS)), IC6.3 (DIR)
X_HOME: IC5.41 (PF0(ADC0)), J9.2, R6.2, R17.1
X_STEP: IC5.30 (PB6(OC1B/!OC4B!/ADC13)), IC6.19 (STEP)
Y_DIR: IC5.29 (PB5(OC1A/!OC4B!/ADC12)), IC7.3 (DIR)
Y_HOME: IC5.40 (PF1(ADC1)), J9.4, R5.2, R18.1
Y_STEP: IC5.28 (PB4(ADC11)), IC7.19 (STEP)
Z_DIR: IC5.31 (PC6(OC3A/!OC4A!)), J2.4
Z_HOME: IC5.1 (PE6), J9.6, R4.2, R19.1
Z_STEP: IC5.32 (PC7(ICP3/CLK0/OC4A)), J2.5

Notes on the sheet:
CNC Plotter Controller
V0.5 (02/06/2012)
(C) 2012 Luke Weston
Released under the CERN Open Hardware License: www.ohwr.org/cernohl
github.com/lukeweston/CNCPlotter

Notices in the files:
parts and their libraries:
freetronics-original: Licensing: CC v3.0 Share-Alike You are welcome to use this library for commercial purposes.
